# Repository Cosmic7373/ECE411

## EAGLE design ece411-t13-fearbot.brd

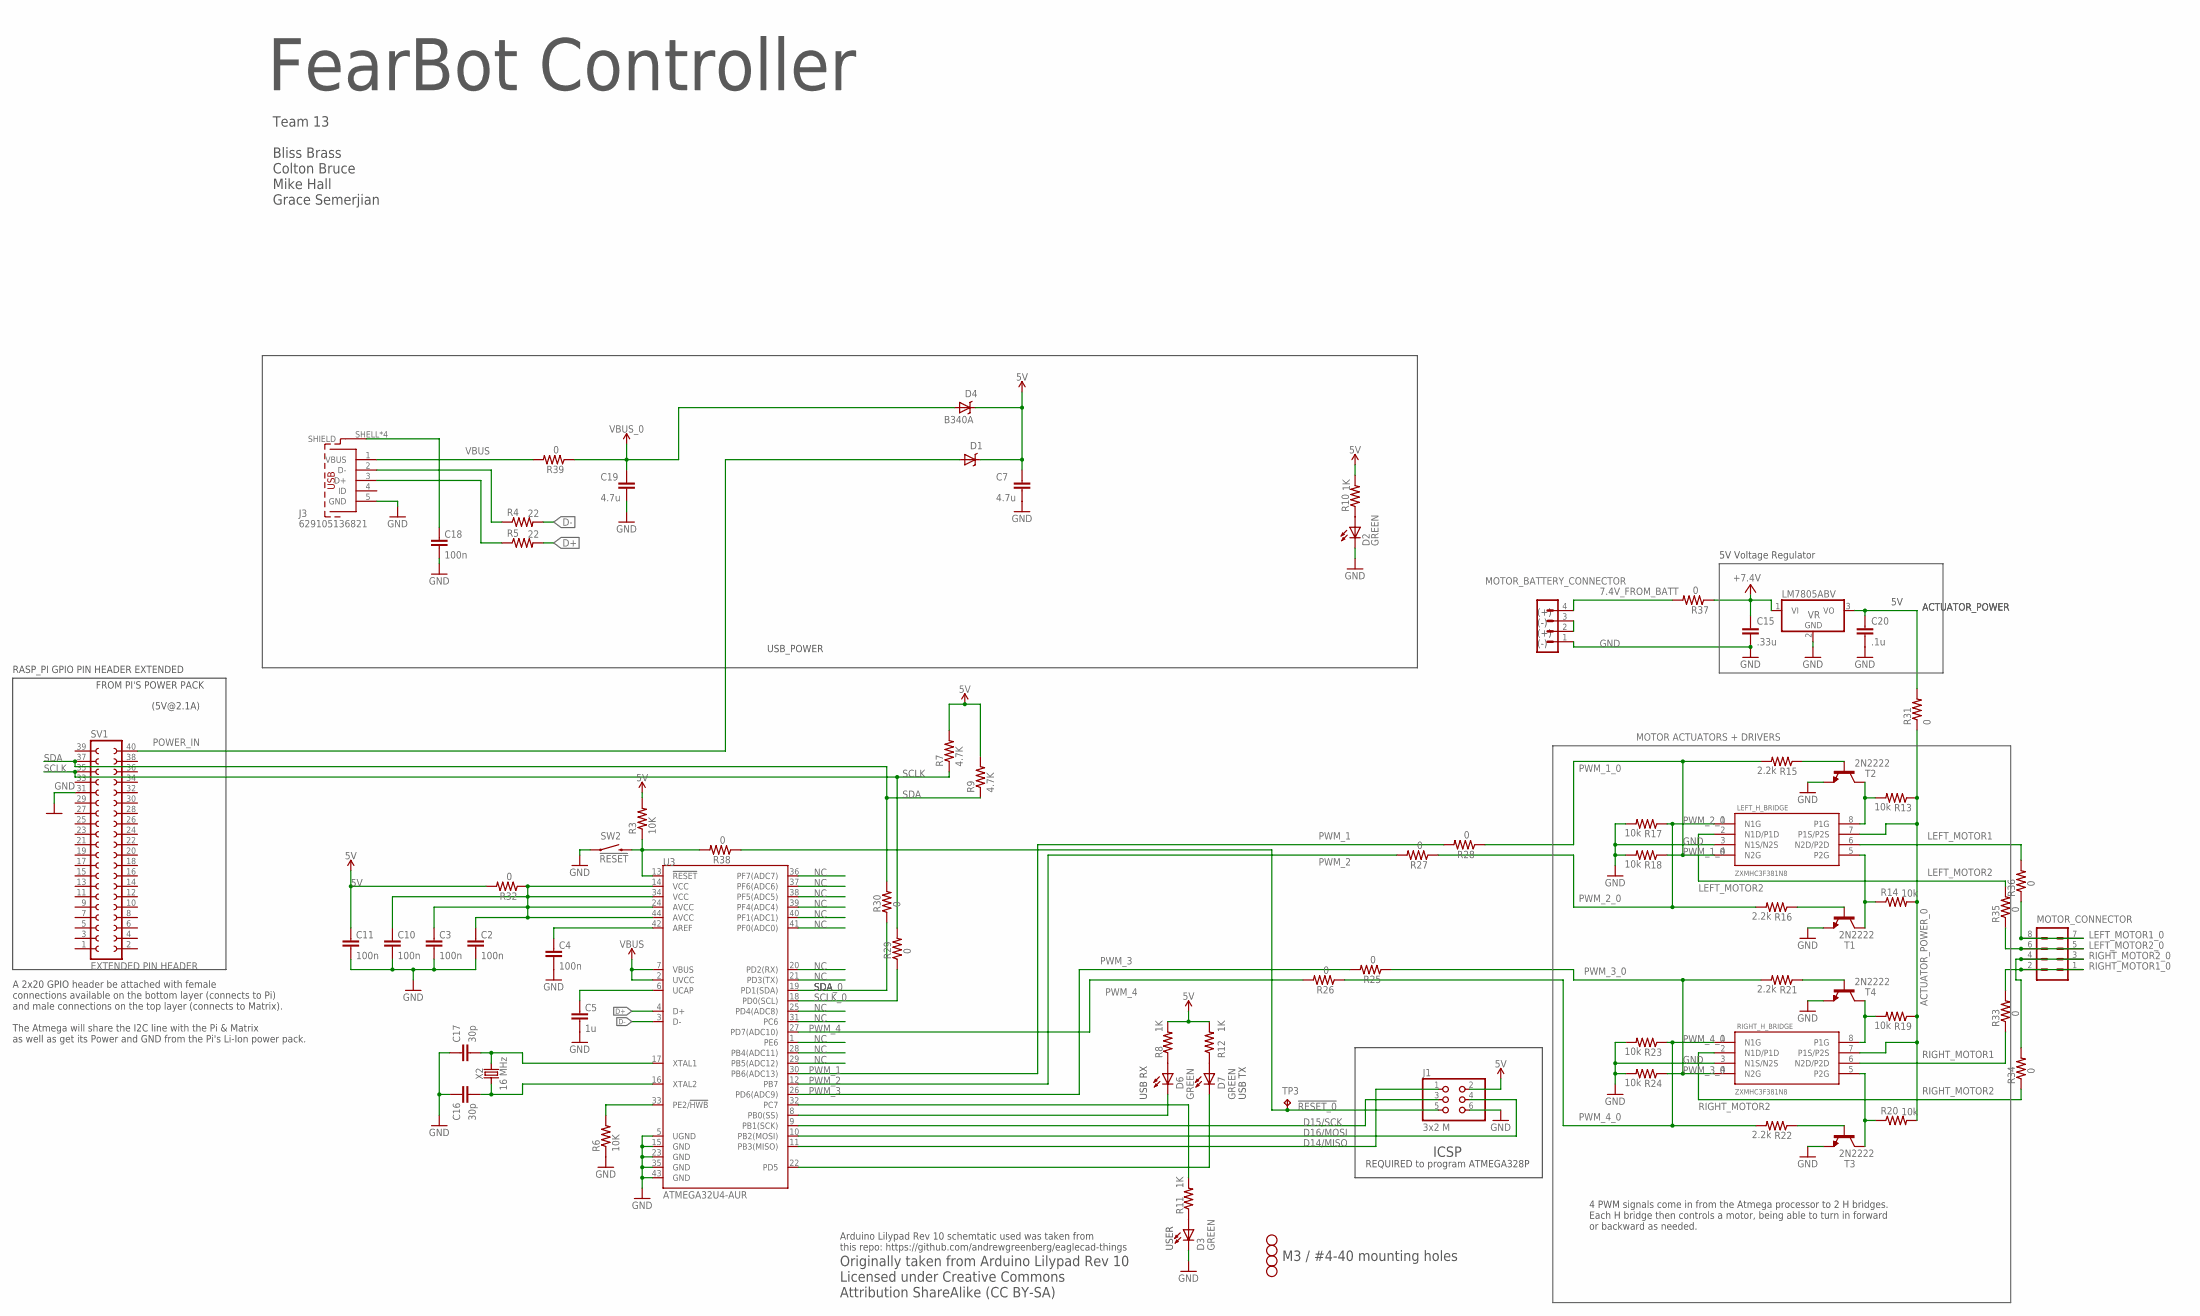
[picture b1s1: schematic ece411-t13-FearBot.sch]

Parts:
C2, C3, C4, C10, C11, C18: 100n; C0805K; MPN CL21B104KBCNNNC
C5: 1u; C0805K; MPN CL21B105KOFNNNG
C7, C19: 4.7u; C0805K; MPN CL21A475KOFNNNE
C15: .33u; C2.5-3
C16, C17: 30p; C0805K; MPN CL21C180JBANNNC
C20: .1u; C2.5-3
D1, D4: B340A; SMA-DIODE; MPN B340AE-13
D2, D3, D6, D7: GREEN; CHIP-LED0805; MPN 150080GS75000
H1, H2, H3, H4: STAND-OFF
J1: 3x2 M; 2X03; MPN M20-9980345
J3: 629105136821; MPN 629105136821
LEFT_H_BRIDGE: ZXMHC3F381N8; SOIC8
MOTOR_BATTERY_CONNECTOR: MOTOR_BATTERY_CONNECTOR; MA04-1
MOTOR_CONNECTOR: MOTOR_CONNECTOR; MA04-2
R3, R6: 10K; R0805; MPN RC0805FR-0710KL
R4, R5: 22; R0805; MPN RC0805FR-0722RL
R7, R9: 4.7K; R0805; MPN RC0805FR-0710KL
R8, R10, R11, R12: 1K; R0805; MPN RC0805FR-071KL
R13, R14, R17, R18, R19, R20, R23, R24: 10k; R0805; MPN RC0805FR-071KL
R15, R16, R21, R22: 2.2k; R0805; MPN RC0805FR-071KL
R25, R26, R27, R28, R29, R30, R31, R32, R33, R34, R35, R36, R37, R38, R39: 0; 0207/2V; MPN RC0805FR-0710KL
RIGHT_H_BRIDGE: ZXMHC3F381N8; SOIC8
SV1: EXTENDED PIN HEADER; FE20-2
SW2: !RESET; TACTILE_SWITCH_SMD; MPN RS-187R05A2-DS MT RT
T1, T2, T3, T4: 2N2222; TO92-EBC-OVAL
TP3: TPPAD1-13; P1-13
U3: ATMEGA32U4-AUR; TQFP44; MPN ATMEGA32U4-AUR
VR: LM7805ABV; TO220H
X2: 16 MHz; HC49UP; MPN ECS-160-18-5PX-TR

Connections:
5V: C7.1, C11.1, D1.C, D4.C, J1.2, R3.2, R7.2, R8.2, R9.2, R10.2, R12.2, R32.2
5V_0: C2.1, C3.1, C10.1, R32.1, U3.14 (VCC), U3.24 (AVCC), U3.34 (VCC), U3.44 (AVCC)
7.4V_FROM_BATT: MOTOR_BATTERY_CONNECTOR.4, R37.2
7.4_FROM_BATT_0: C15.1, R37.1, VR.1 (VI)
!RESET: R3.1, R38.2, SW2.3 (2), U3.13 (!RESET)
!RESET_0: J1.5, R38.1, TP3.TP
ACTUATOR_POWER: C20.1, R31.2, VR.3 (VO)
ACTUATOR_POWER_0: LEFT_H_BRIDGE.7 (P1S/P2S), R13.1, R14.2, R19.1, R20.2, R31.1, RIGHT_H_BRIDGE.7 (P1S/P2S)
AREF: C4.1, U3.42 (AREF)
D13#/USER_LED: R11.2, U3.32 (PC7)
D14/MISO: J1.1, U3.11 (PB3(MISO))
D15/SCK: J1.3, U3.9 (PB1(SCK))
D16/MOSI: J1.4, U3.10 (PB2(MOSI))
D17/RX-LED: D6.C, U3.8 (PB0(SS))
D+: R5.2, U3.4 (D+)
D-: R4.2, U3.3 (D-)
GND: C2.2, C3.2, C4.2, C5.2, C7.2, C10.2, C11.2, C15.2, C16.2, C17.2, C18.2, C19.2, C20.2, D2.C, D3.C, J1.6, J3.5 (GND), LEFT_H_BRIDGE.3 (N1S/N2S), MOTOR_BATTERY_CONNECTOR.1, R6.1, R17.2, R18.2, R23.2, R24.2, RIGHT_H_BRIDGE.3 (N1S/N2S), SV1.31, SW2.1, T1.E, T2.E, T3.E, T4.E, U3.5 (UGND), U3.15 (GND), U3.23 (GND), U3.35 (GND), U3.43 (GND), VR.2 (GND)
LEFT_MOTOR1: LEFT_H_BRIDGE.6 (N2D/P2D), R36.2
LEFT_MOTOR1_0: MOTOR_CONNECTOR.7, MOTOR_CONNECTOR.8, R36.1
LEFT_MOTOR2: LEFT_H_BRIDGE.2 (N1D/P1D), R35.2
LEFT_MOTOR2_0: MOTOR_CONNECTOR.5, MOTOR_CONNECTOR.6, R35.1
unnamed: MOTOR_BATTERY_CONNECTOR.2, MOTOR_BATTERY_CONNECTOR.3
unnamed: D2.A, R10.1
unnamed: LEFT_H_BRIDGE.5 (P2G), R14.1, T1.C
unnamed: LEFT_H_BRIDGE.8 (P1G), R13.2, T2.C
unnamed: R15.1, T2.B
unnamed: R16.1, T1.B
unnamed: D3.A, R11.1
unnamed: C18.1, J3.SHELL (SHIELD), J3.SHELL1 (SHIELD), J3.SHELL2 (SHIELD), J3.SHELL3 (SHIELD)
unnamed: D6.A, R8.1
unnamed: D7.A, R12.1
unnamed: R20.1, RIGHT_H_BRIDGE.5 (P2G), T3.C
unnamed: R19.2, RIGHT_H_BRIDGE.8 (P1G), T4.C
unnamed: J3.2 (D-), R4.1
unnamed: J3.3 (D+), R5.1
unnamed: R21.1, T4.B
unnamed: R22.1, T3.B
NC: U3.20 (PD2(RX)), U3.21 (PD3(TX))
PE2/!HWB: R6.2, U3.33 (PE2/!HWB)
POWER_IN: D1.A, SV1.40
PWM_1: R28.2, U3.30 (PB6(ADC13))
PWM_1_0: LEFT_H_BRIDGE.4 (N2G), R15.2, R18.1, R28.1
PWM_2: R27.2, U3.12 (PB7)
PWM_2_0: LEFT_H_BRIDGE.1 (N1G), R16.2, R17.1, R27.1
PWM_3: R25.2, U3.26 (PD6(ADC9))
PWM_3_0: R21.2, R24.1, R25.1, RIGHT_H_BRIDGE.4 (N2G)
PWM_4: R26.2, U3.27 (PD7(ADC10))
PWM_4_0: R22.2, R23.1, R26.1, RIGHT_H_BRIDGE.1 (N1G)
RIGHT_MOTOR1: R33.1, RIGHT_H_BRIDGE.6 (N2D/P2D)
RIGHT_MOTOR1_0: MOTOR_CONNECTOR.1, MOTOR_CONNECTOR.2, R33.2
RIGHT_MOTOR2: R34.1, RIGHT_H_BRIDGE.2 (N1D/P1D)
RIGHT_MOTOR2_0: MOTOR_CONNECTOR.3, MOTOR_CONNECTOR.4, R34.2
SCLK: R7.1, R29.2, SV1.35
SCLK_0: R29.1, U3.18 (PD0(SCL))
SDA: R9.1, R30.2, SV1.37
SDA_0: R30.1, U3.19 (PD1(SDA))
TX_LED: D7.C, U3.22 (PD5)
UCAP: C5.1, U3.6 (UCAP)
VBUS: J3.1 (VBUS), R39.2, U3.2 (UVCC), U3.7 (VBUS)
VBUS_0: C19.1, D4.A, R39.1
XTAL1: C17.1, U3.17 (XTAL1), X2.2
XTAL2: C16.1, U3.16 (XTAL2), X2.1

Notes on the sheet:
Originally taken from Arduino Lilypad Rev 10 Licensed under Creative Commons Attribution ShareAlike (CC BY-SA)
M3 / #4-40 mounting holes
ICSP
REQUIRED to program ATMEGA328P
USB RX
USB TX
USER
MOTOR ACTUATORS + DRIVERS
USB_POWER
(5V@2.1A)
RASP_PI GPIO PIN HEADER EXTENDED
A 2x20 GPIO header be attached with female connections available on the bottom layer (connects to Pi) and male connections on the top layer (connects to Matrix). The Atmega will share the I2C line with the Pi & Matrix as well as get its Power and GND from the Pi's Li-Ion power pack.
FROM PI'S POWER PACK
Arduino Lilypad Rev 10 schemtatic used was taken from this repo: https://github.com/andrewgreenberg/eaglecad-things
(+)
(-)
5V Voltage Regulator
4 PWM signals come in from the Atmega processor to 2 H bridges. Each H bridge then controls a motor, being able to turn in forward or backward as needed.
FearBot Controller
Team 13 Bliss Brass Colton Bruce Mike Hall Grace Semerjian

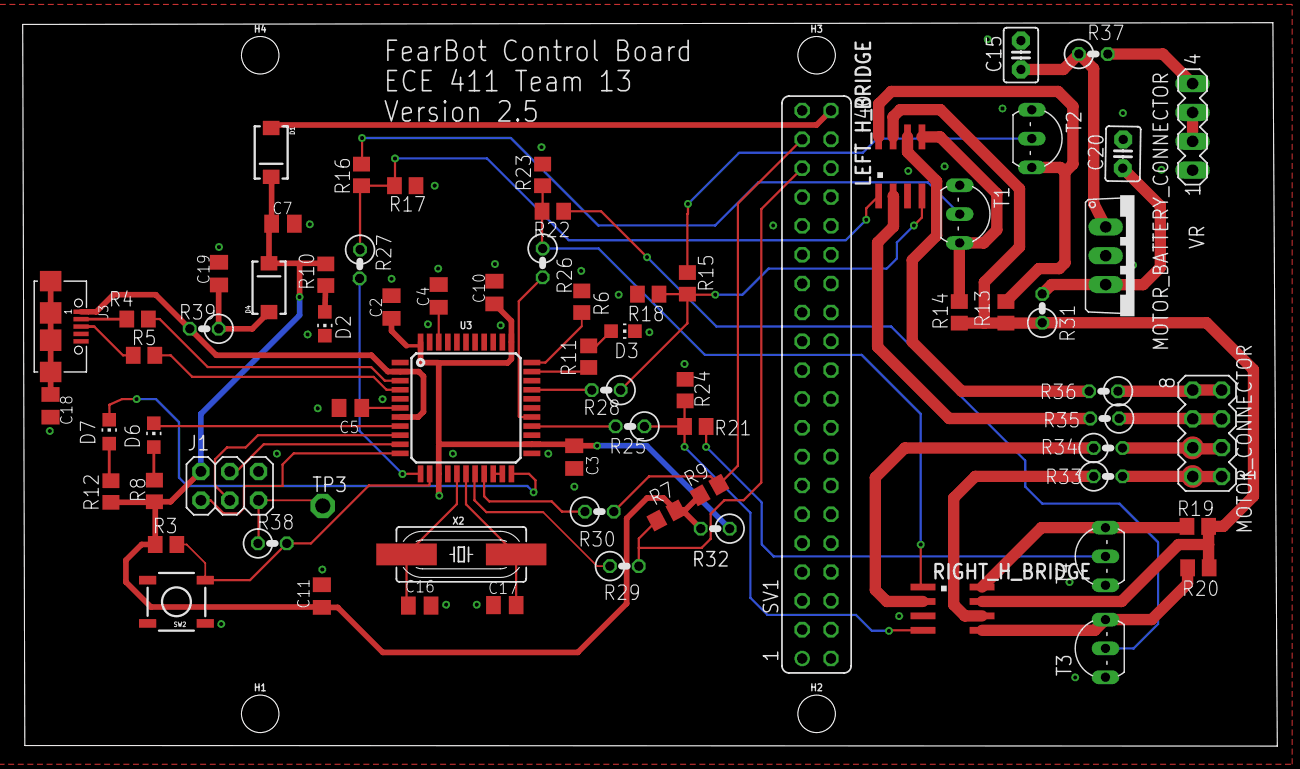
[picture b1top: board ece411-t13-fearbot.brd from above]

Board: 2 copper layers, 110.5 x 63.7 mm, 76 parts (0 on the bottom side), 62 nets.

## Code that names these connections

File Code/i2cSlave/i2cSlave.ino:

// Bliss 
// 11-29-19
// Bliss Brass
// ECE 411
// Turning the ItsyBitsy 32u4 3V breakout board into a I2C Slave and controlling outputs
// Be sure to select the Itsy Bitsy 32u4 3V board in the Tools menu

#include <Wire.h>

int z = 370;
int control1 = 13;
int control2 = 9;
int control3 = 10;
int control4 = 6;

int brightness = 0;
int fadeAmount = 5;

void setup() {
  Wire.begin(4);                   // Turning Atmega into a slave on address 0x04
  Wire.onReceive(receiveEvent);    // On start sequence call function
  Serial.begin(9600);              // Set the Baud rate

  pinMode(control1, OUTPUT);
  pinMode(control2, OUTPUT);
  pinMode(control3, OUTPUT);
  //pinMode(control4, OUTPUT);
  // PB6 Pin 30 and PB7 Pin 12 paired
  // PD6 Pin 26 and PD7 Pin 27 Paired
}

void loop() {
  //delay(100);
  // Noise is to the ??? turn
  if ((360 >= z) && (z > 200)) {
    for (int i = 10000; i > 0; i--) {  
      analogWrite(control1, 255);
      delayMicroseconds(50);  // Delaying 50 Micro Seconds
      analogWrite(control1, 0);
      delayMicroseconds(50);
    }
    z = 370;  // Setting Z outside the trigger range
    /*analogWrite(control1, brightness);
    brightness = brightness + fadeAmount;
    if (brightness <= 0 || brightness >= 255) {
      fadeAmount = -fadeAmount;
    }
    delay(30);*/
  }
  // Noise is to the ??? turn
  else if ((z >= 0) && (z < 160)) {
    for (int i = 10000; i > 0; i--) {  
      analogWrite(control2, 255);
      delayMicroseconds(50);  // Delaying 50 Micro Seconds
      analogWrite(control2, 0);
      delayMicroseconds(50);
    }
    z = 370;  // Setting Z outside the trigger range
  }

  // Noise is behind drive straight 
  else if ((200 >= z) && (z >= 160)) {
    for (int i = 10000; i > 0; i--) {  
      analogWrite(control3, 255); // Setting V to max (Voltage)
      delayMicroseconds(50);      // Delaying 50 Micro Seconds for PWM
      analogWrite(control3, 0);   // Setting V to 0
      delayMicroseconds(50);
    }
    z = 370;  // Setting Z outside the trigger range
  }
  else {
    
  }
}

void receiveEvent(int howMany) {
  // Loop through all sent bytes
  String buff;
  
  while(0 < Wire.available()) {
    char c = Wire.read();
    //Serial.print(c);
    buff = buff + c;
  }
  Serial.println(buff);
  
  z = buff.toInt();
  Serial.print("Z is ");
  Serial.println(z);

}

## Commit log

2019-10-17 Create LICENSE
2019-10-22 Commit test of expenditures
2019-10-24 Uploading HW3
2019-10-29 I started the schematic, it's got some Rasp Pi components and the Matrix Voice's FPGA on there
2019-10-30 I think that I'm almost done with the schematic
    It needs the Li-Ion for the Matrix/Rasp/ATMega
2019-10-30 Added in power supply, reduced PWM channels, added in UART (from ATmega), and converted H Bridges
2019-10-31 Updated Expenditures Spreadsheet
2019-10-31 Pic of the breadboard prototype
2019-10-31 Video of chassis moving
2019-10-31 Expenditures Update
2019-10-31 Adding invoice for board components, and updating expenditures
2019-11-01 Blarg test
2019-11-02 Updated Expenditures and added Digi-Key order invoice
2019-11-02 Added 3 ATmega Datasheets
2019-11-05 Upload Schedule Rough Draft
2019-11-06 Updated Schedule with Bliss and Mike Task Assignments
2019-11-07 Change dates and modify assignments
2019-11-07 Added in the H Bridge ICs and removed what was before
2019-11-07 This was the functional schematic that I used to build the preliminary pcb
2019-11-07 The preliminary pcb itself
2019-11-07 Project Schedule Attempt
2019-11-13 Uploading initial draft of BOM
2019-11-14 Add design block diagram
2019-11-14 Inluded H-bridge ICs, more connectors, and replaced UART with I2C
2019-11-14 PCB layout of schematic, and now has flooded gnds on both layers
2019-11-14 Adding BOM
2019-11-16 Added in connector for Pi to ATMega as well as battery for the schematic
    Mounting holes line up (more or less) with the Pi now
    We still need the right H Bridge Driver ICs, check GNDing, adding in vias for ea. GND connection, and check up on decoupling caps for power sources
2019-11-16 Added Expenditure
2019-11-16 Added breakouts to Bliss's expenditures
2019-11-16 Added H-Bridge IC and topology to schematic
2019-11-16 Added H-Bridge to Board
2019-11-17 Board tweaks- spacing and right angle approaches to pads
2019-11-18 Fixed routing mistakes, extended board edge to clear matrix
2019-11-19 Added in 0ohm resistors and added in vias (for stitching)
    GND Plane is still a question mark, vias don't seem to be part of flooded planes. Also DRC claims GND pins aren't connected to GND plane
2019-11-20 Updated Expenditures
2019-11-20 Changed 0ohm resistors to through hole
2019-11-21 Changed just about everything
    Jk, changed wire widths, stitched properly, passed ERC as well as DRC
2019-11-21 Made board slimmer, changed mask tab's limit, and included diff. DRU (Laen)
2019-11-21 Traces orthogonal to pads, schematic title, frame value, motor pin de-fucking.
2019-11-21 De-de-fucked motor header connections
2019-11-21 Neutralized Silkscreen Menace
2019-11-21 Uploading final board/schematic
2019-11-21 Rename board and add design review
2019-11-21 Changing voltage regulator to vertical footprint to correct extra hole.
2019-11-21 Adding Final Board Version Submitted to OSHPark
    Changed to vertical footprint for v-regulator to fix hole issue
2019-11-25 Deleting just txt file and adding HW6 Physical layer things.
2019-11-26 Organizing
2019-12-07 Add Test plan
2019-12-09 Uploading Arduino Code
    Control Code for the Atmega32u4 as well as test code for the ItsyBitsy breakout board and a i2c detect function for the Arduino side
2019-12-09 Ripped from Pi code to Code folder
2019-12-10 Modified ATMega code timing
2019-12-12 Organized Documents
2019-12-12 Modified Code (add turn and move)
2019-12-13 Modified Code Timing

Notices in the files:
parts and their libraries:
SparkFun-PowerSymbols: Licensing: Creative Commons ShareAlike 4.0 International - https://creativecommons.org/licenses/by-sa/4.0
SparkFun-Electromechanical: Licensing: CC v3.0 Share-Alike You are welcome to use this library for commercial purposes.
